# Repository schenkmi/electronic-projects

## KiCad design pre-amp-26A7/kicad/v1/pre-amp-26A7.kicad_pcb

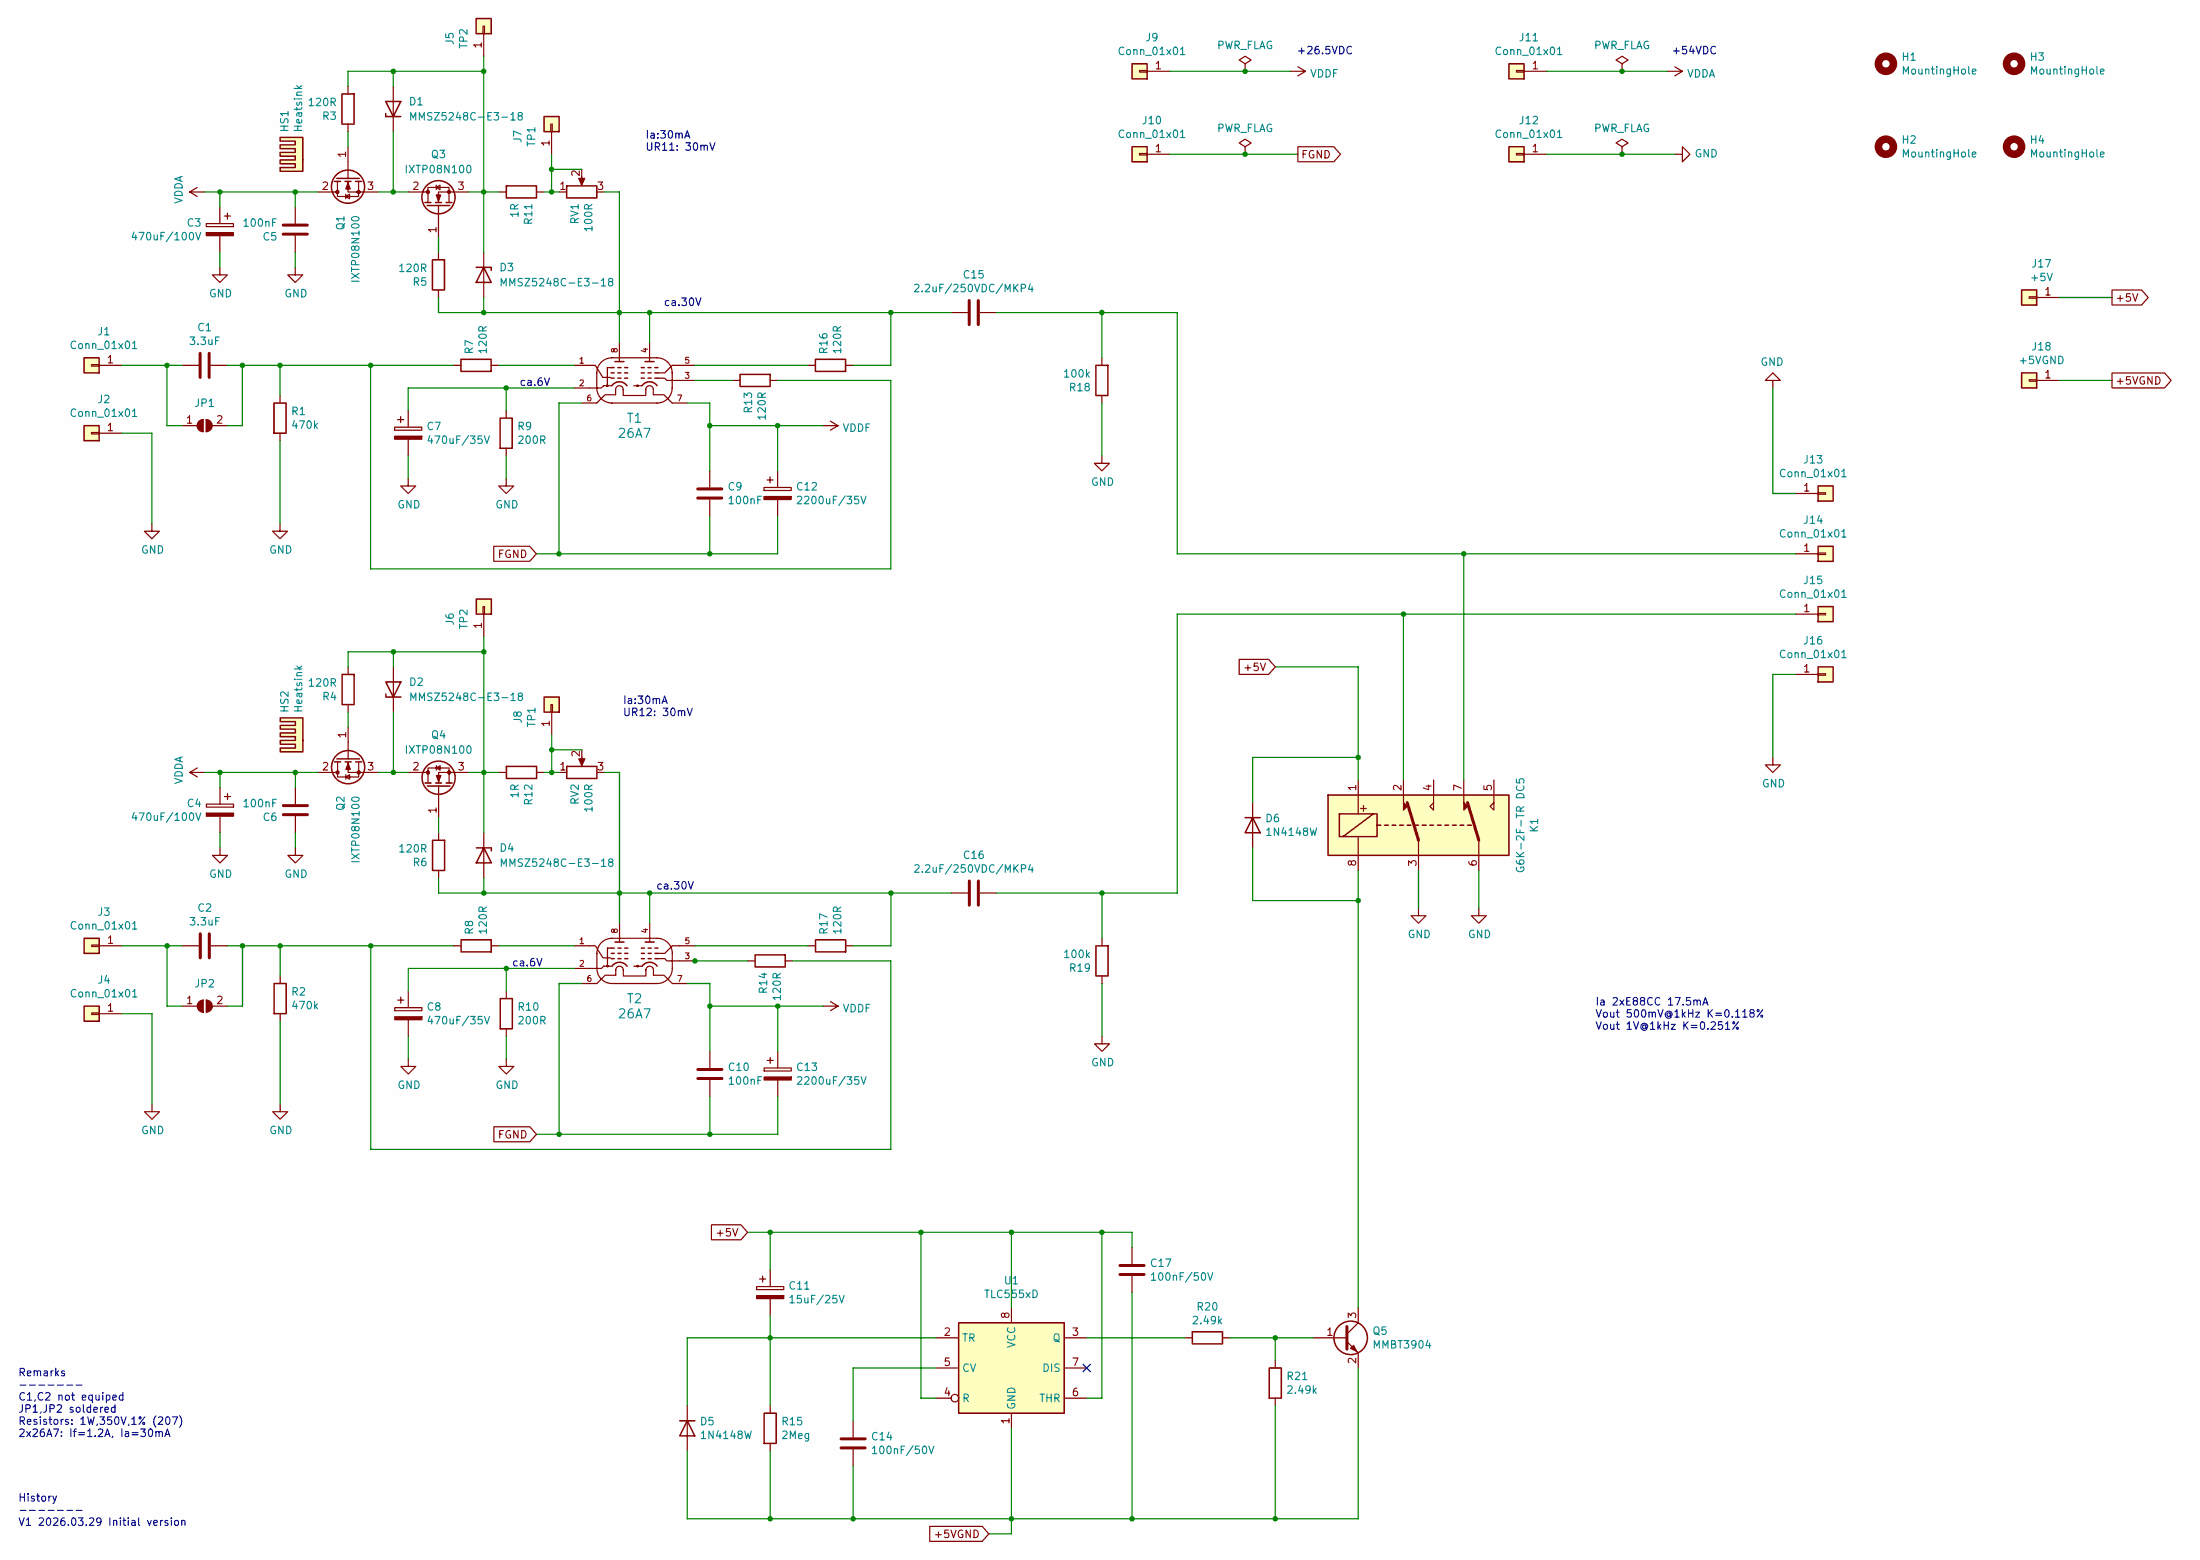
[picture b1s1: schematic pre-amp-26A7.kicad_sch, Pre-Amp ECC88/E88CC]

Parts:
C1, C2: 3.3uF; C_Rect_L7.2mm_W7.2mm_P5.00mm_FKS2_FKP2_MKS2_MKP2
C3, C4: 470uF/100V; CP_Radial_D18.0mm_P7.50mm
C5, C6, C9, C10: 100nF; C_Rect_L7.2mm_W2.5mm_P5.00mm_FKS2_FKP2_MKS2_MKP2
C7, C8: 470uF/35V; CP_Radial_D10.0mm_P5.00mm
C11: 15uF/25V; CP_EIA-3216-12_Kemet-S_HandSolder
C12, C13: 2200uF/35V; CP_Radial_D16.0mm_P7.50mm
C14, C17: 100nF/50V; C_0805_2012Metric_Pad1.18x1.45mm_HandSolder
C15, C16: 2.2uF/250VDC/MKP4; C_Rect_L31.5mm_W11.0mm_P27.50mm_MKS4
D1, D2, D3, D4: MMSZ5248C-E3-18; D_SOD-123
D5, D6: 1N4148W; D_SOD-123
H1, H2, H3, H4: MountingHole; MountingHole_3.2mm_M3_Pad_Via
HS1, HS2: Heatsink; Heatsink_Fischer_SK104-STC-STIC_35x13mm_2xDrill2.5mm
J1, J2, J3, J4, J13, J14, J15, J16: Conn_01x01; Pin_D1.0mm_L10.0mm
J5, J6: TP2; Pin_D1.0mm_L10.0mm
J7, J8: TP1; Pin_D1.0mm_L10.0mm
J9, J10, J11, J12: Conn_01x01; Pin_D1.3mm_L11.0mm
J17: +5V; Pin_D1.3mm_L11.0mm
J18: +5VGND; Pin_D1.3mm_L11.0mm
JP1, JP2: SolderJumper_2_Open; SolderJumper-2_P1.3mm_Open_Pad1.0x1.5mm
K1: G6K-2F-TR DC5; Relay_DPDT_Omron_G6K-2F
Q1, Q2, Q3, Q4: IXTP08N100; TO-220-3_Vertical
Q5: MMBT3904; SOT-23
R1, R2: 470k; R_MELF_MMB-0207
R3, R4, R5, R6, R7, R8, R13, R14, R16, R17: 120R; R_MELF_MMB-0207
R9, R10: 200R; R_MELF_MMB-0207
R11, R12: 1R; R_MELF_MMB-0207
R15: 2Meg; R_0805_2012Metric_Pad1.20x1.40mm_HandSolder
R18, R19: 100k; R_MELF_MMB-0207
R20, R21: 2.49k; R_0805_2012Metric_Pad1.20x1.40mm_HandSolder
RV1, RV2: 100R; Potentiometer_Bourns_3296W_Vertical
T1, T2: 26A7; TubeOctal
U1: TLC555xD; SOIC-8_3.9x4.9mm_P1.27mm

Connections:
+5V: C11.1, C17.1, D6.1 (K), J17.1 (Pin_1_1), K1.1, U1.4 (R), U1.6 (THR), U1.8 (VCC)
+5VGND: C14.2, C17.2, D5.2 (A), J18.1 (Pin_1_1), Q5.2 (E), R15.2, R21.2, U1.1 (GND)
FGND: C9.2, C10.2, C12.2, C13.2, J10.1 (Pin_1_1), T1.6 (h), T2.6 (h)
GND: C3.2, C4.2, C5.1, C6.1, C7.2, C8.2, J2.1 (Pin_1_1), J4.1 (Pin_1_1), J12.1 (Pin_1_1), J13.1 (Pin_1_1), J16.1 (Pin_1_1), K1.3, K1.6, R1.2, R2.2, R9.2, R10.2, R18.1, R19.1
unnamed: D1.2 (A), D3.1 (K), J5.1 (Pin_1_1), Q3.3 (S), R3.2, R11.2
unnamed: D1.1 (K), Q1.3 (S), Q3.2 (D)
unnamed: D2.2 (A), D4.1 (K), J6.1 (Pin_1_1), Q4.3 (S), R4.2, R12.2
unnamed: D2.1 (K), Q2.3 (S), Q4.2 (D)
unnamed: C15.2, D3.2 (A), R5.1, R16.2, RV1.3, T1.4 (p), T1.8 (p)
unnamed: C16.2, D4.2 (A), R6.1, R17.2, RV2.3, T2.4 (p), T2.8 (p)
unnamed: C11.2, D5.1 (K), R15.1, U1.2 (TR)
unnamed: D6.2 (A), K1.8, Q5.3 (C)
unnamed: C1.2, J1.1 (Pin_1_1), JP1.1 (A)
unnamed: C2.2, J3.1 (Pin_1_1), JP2.1 (A)
unnamed: J7.1 (Pin_1_1), R11.1, RV1.1, RV1.2
unnamed: J8.1 (Pin_1_1), R12.1, RV2.1, RV2.2
unnamed: C15.1, J14.1 (Pin_1_1), K1.7, R18.2
unnamed: C16.1, J15.1 (Pin_1_1), K1.2, R19.2
unnamed: C1.1, JP1.2 (B), R1.1, R7.1, R13.2
unnamed: C2.1, JP2.2 (B), R2.1, R8.1, R14.2
unnamed: Q1.1 (G), R3.1
unnamed: Q2.1 (G), R4.1
unnamed: Q3.1 (G), R5.2
unnamed: Q4.1 (G), R6.2
unnamed: Q5.1 (B), R20.1, R21.1
unnamed: R7.2, T1.1 (s)
unnamed: R8.2, T2.1 (s)
unnamed: R16.1, T1.5 (s)
unnamed: R17.1, T2.5 (s)
unnamed: R13.1, T1.3 (g)
unnamed: C7.1, R9.1, T1.2 (ks)
unnamed: R14.1, T2.3 (g)
unnamed: C8.1, R10.1, T2.2 (ks)
unnamed: C14.1, U1.5 (CV)
unnamed: R20.2, U1.3 (Q)
VDDA: C3.1, C4.1, C5.2, C6.2, J11.1 (Pin_1_1), Q1.2 (D), Q2.2 (D)
VDDF: C9.1, C10.1, C12.1, C13.1, J9.1 (Pin_1_1), T1.7 (h), T2.7 (h)

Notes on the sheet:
Remarks ------- C1,C2 not equiped JP1,JP2 soldered Resistors: 1W,350V,1% (207) 2x26A7: If=1.2A, Ia=30mA
ca.30V
Ia 2xE88CC 17.5mA Vout 500mV@1kHz K=0.118% Vout 1V@1kHz K=0.251%
Ia:30mA UR12: 30mV
History ------- V1 2026.03.29 Initial version
ca.6V
+26.5VDC
+54VDC
Ia:30mA UR11: 30mV

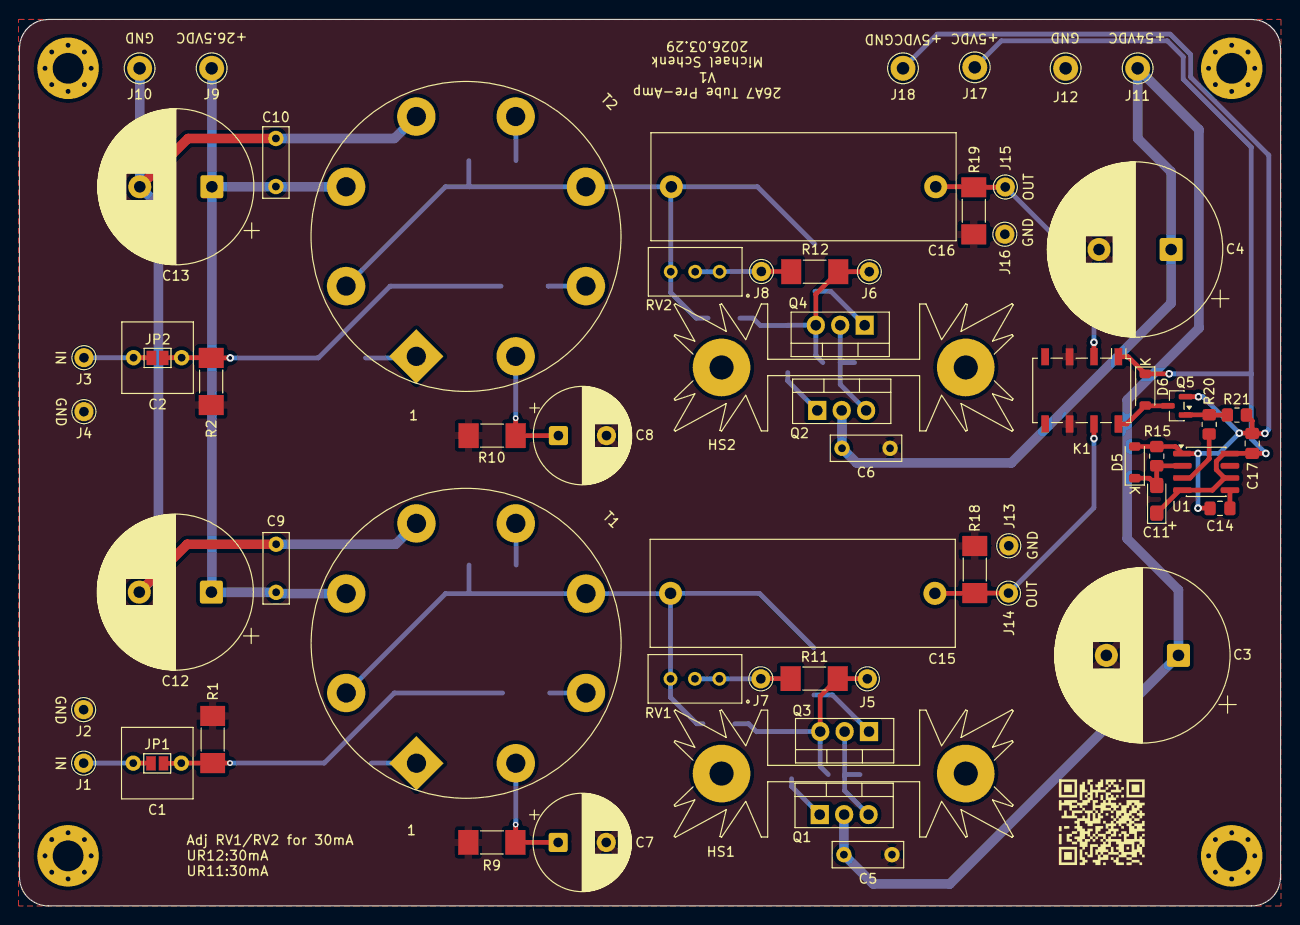
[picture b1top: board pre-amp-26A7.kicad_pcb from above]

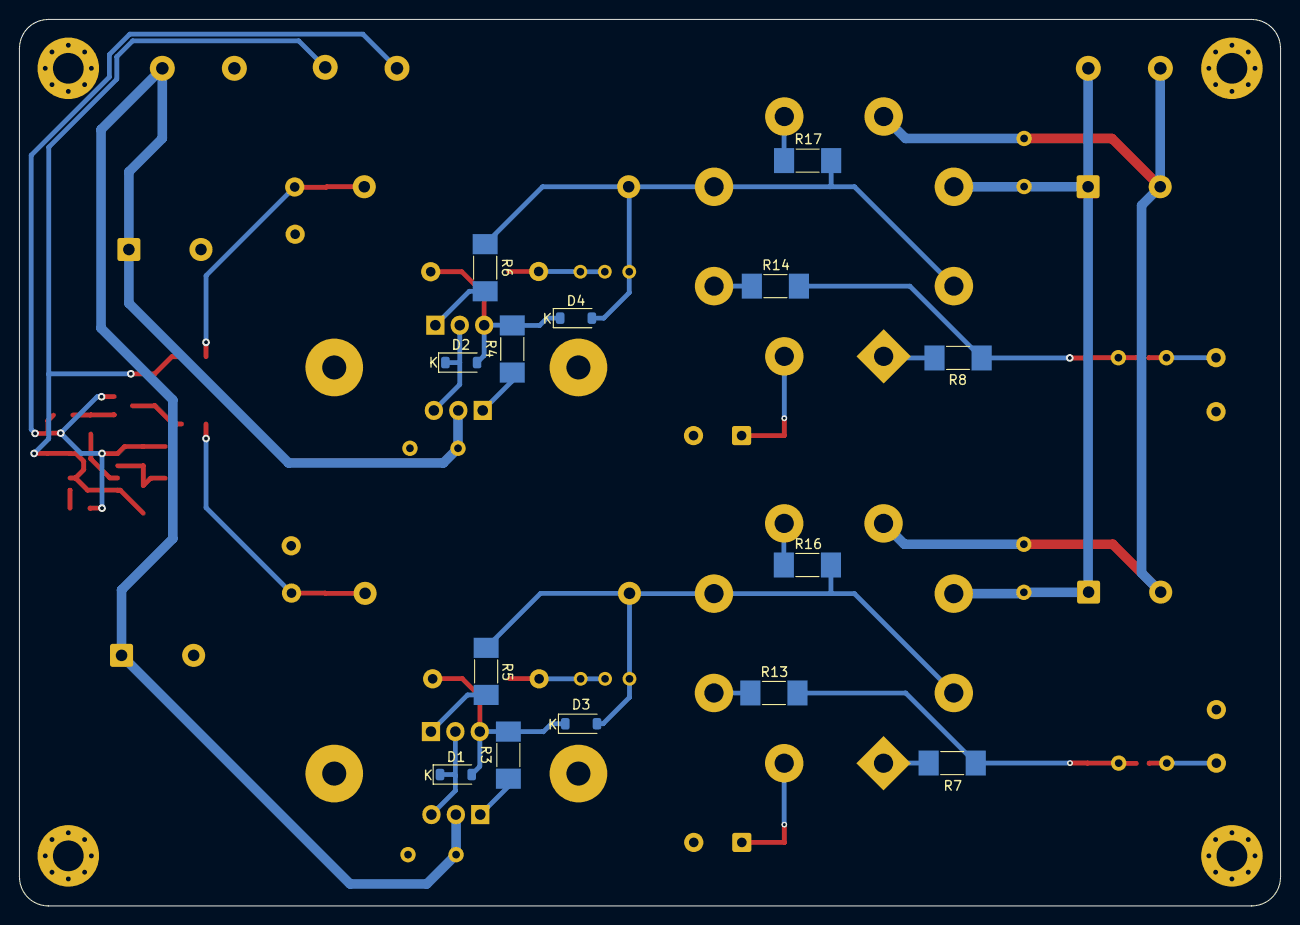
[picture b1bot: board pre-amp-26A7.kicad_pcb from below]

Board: 2 copper layers, 131.2 x 92.2 mm, 81 parts (14 on the bottom side), 37 nets.

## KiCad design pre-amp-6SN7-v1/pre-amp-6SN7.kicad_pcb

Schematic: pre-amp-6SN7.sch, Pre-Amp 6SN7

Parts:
C1, C5: 3.3uF; C_Rect_L7.2mm_W7.2mm_P5.00mm_FKS2_FKP2_MKS2_MKP2
C2, C8: 100nF; C_Rect_L18.0mm_W5.0mm_P15.00mm_FKS3_FKP3
C3, C9: 100uF; CP_Radial_D18.0mm_P7.50mm
C4, C10: 2.2uF; C_Rect_L31.5mm_W11.0mm_P27.50mm_MKS4
C6, C11: 100nF; C_Rect_L7.2mm_W2.5mm_P5.00mm_FKS2_FKP2_MKS2_MKP2
C7, C12: 2200uF; CP_Radial_D16.0mm_P7.50mm
D1, D2: 1N4007; D_SOD-123F
H1, H2, H3, H4: MountingHole; MountingHole_3.2mm_M3
J1, J3: IN; Pin_D1.0mm_L10.0mm
J2, J4: GNDIN; Pin_D1.0mm_L10.0mm
J5: HV; Pin_D1.3mm_L11.0mm
J6: GNDHV; Pin_D1.3mm_L11.0mm
J7, J11: OUT; Pin_D1.0mm_L10.0mm
J8, J12: GNDOUT; Pin_D1.0mm_L10.0mm
J9: LV1; Pin_D1.3mm_L11.0mm
J10, J14: GNDLV; Pin_D1.3mm_L11.0mm
J13: LV2; Pin_D1.3mm_L11.0mm
R1, R9, R10, R20: 1Meg; R_MELF_MMB-0207
R2, R11: 47k; R_MELF_MMB-0207
R3, R13: 1k; R_MELF_MMB-0207
R4, R5, R12, R15, R18, R19, R22, R24: 47k/1W; R_MELF_MMB-0207
R6, R17: 100k; R_MELF_MMB-0207
R7, R8, R14, R16: 100R; R_MELF_MMB-0207
T1, T2: 6SN7GT; TubeOctal

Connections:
GND: C2.2, C3.2, C6.2, C7.2, C8.2, C9.2, C11.2, C12.2, J2.1, J4.1, J6.1, J8.1, J10.1, J12.1, J14.1, R1.2, R3.2, R9.2, R10.2, R13.2, R18.2, R19.2, R20.2, R22.2, R24.2, T1.8 (h), T2.8 (h)
unnamed: C1.1, R1.1, R2.2
unnamed: C1.2, J3.1
unnamed: C4.1, J7.1, R6.1, R9.1
unnamed: C4.2, D1.1, R22.1, R24.1, T1.6 (kT2)
unnamed: C5.1, R10.1, R11.2
unnamed: C5.2, J1.1
unnamed: C10.1, J11.1, R17.1, R20.1
unnamed: C10.2, D2.1, R18.1, R19.1, T2.6 (kT2)
unnamed: D1.2, R4.2, R5.2, R8.2, T1.2 (qT1)
unnamed: D2.2, R12.2, R15.2, R16.2, T2.2 (qT1)
unnamed: R2.1, R6.2, R7.2
unnamed: R3.1, T1.3 (kT1)
unnamed: R7.1, T1.1 (gT1)
unnamed: R8.1, T1.4 (gT2)
unnamed: R11.1, R14.2, R17.2
unnamed: R13.1, T2.3 (kT1)
unnamed: R14.1, T2.1 (gT1)
unnamed: R16.1, T2.4 (gT2)
VDDA: C2.1, C3.1, C8.1, C9.1, J5.1, R4.1, R5.1, R12.1, R15.1, T1.5 (qT2), T2.5 (qT2)
VDDF1: C11.1, C12.1, J9.1, T1.7 (h)
VDDF2: C6.1, C7.1, J13.1, T2.7 (h)

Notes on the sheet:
LV: 6.3VDC / 1.2A HV: 300VDC / 26mA

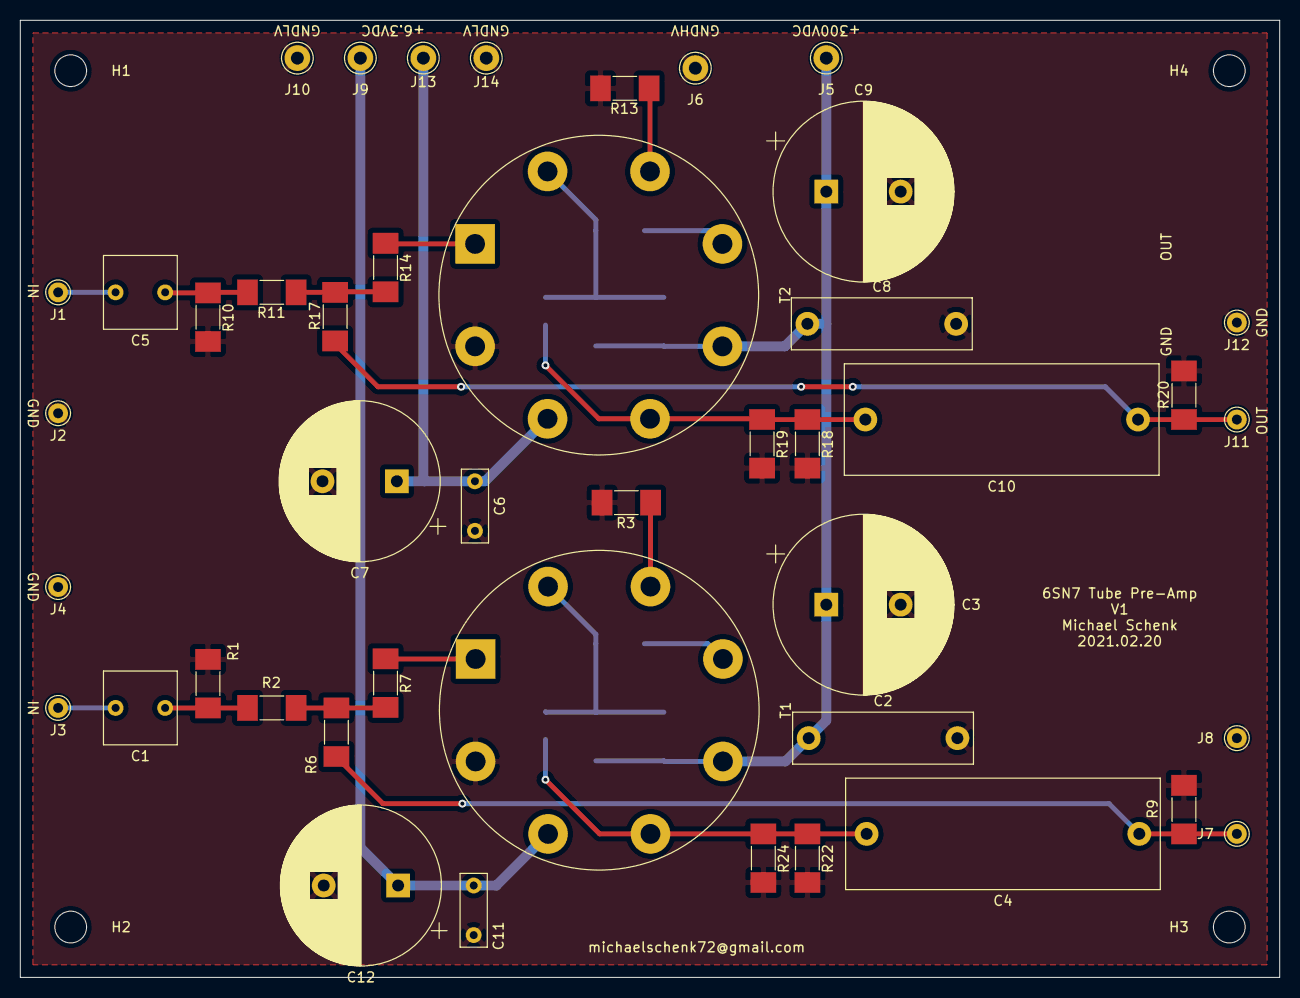
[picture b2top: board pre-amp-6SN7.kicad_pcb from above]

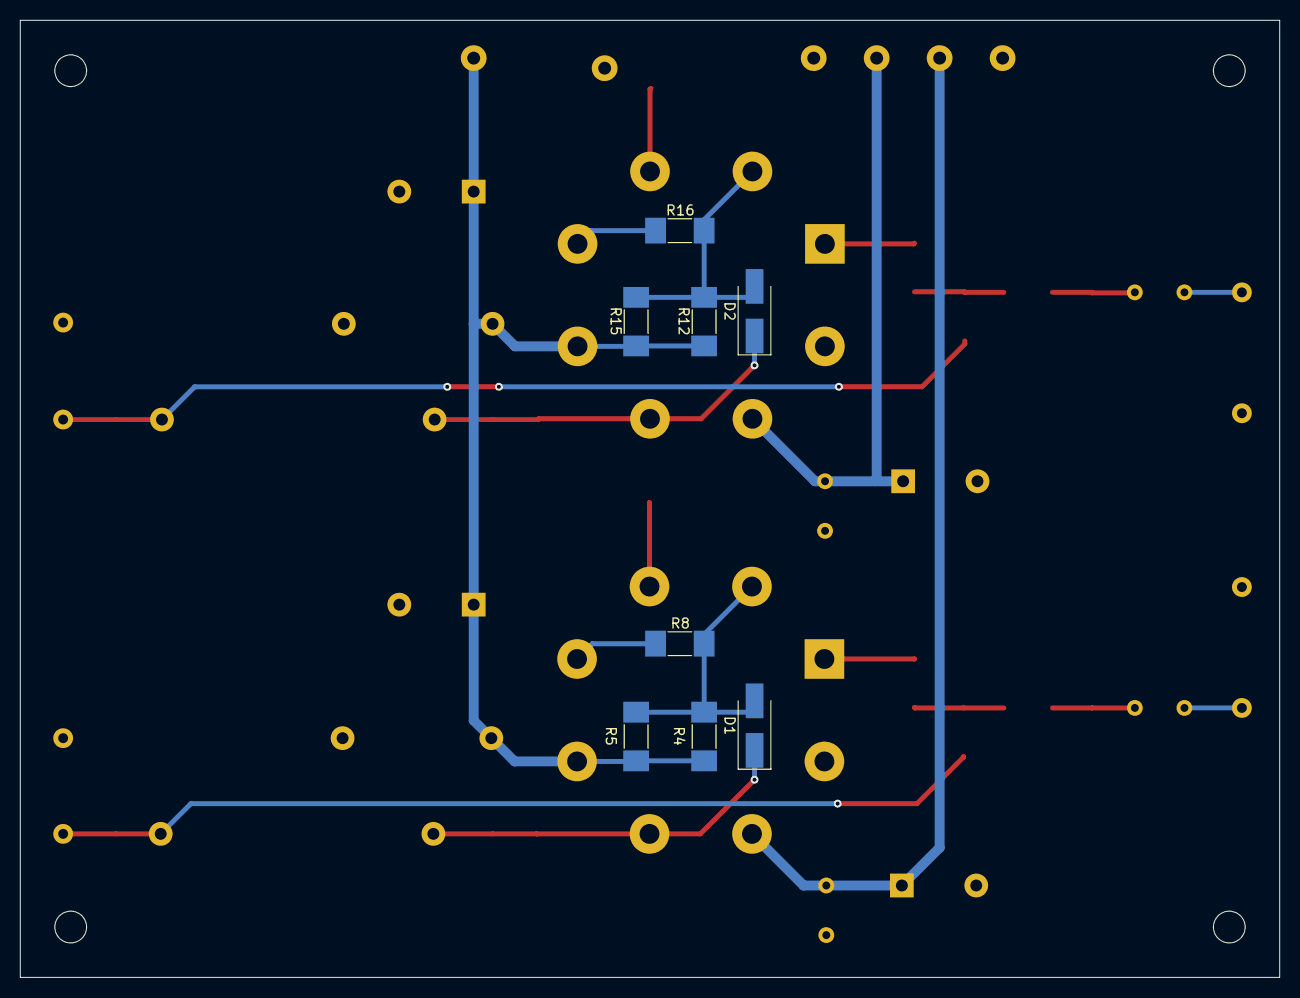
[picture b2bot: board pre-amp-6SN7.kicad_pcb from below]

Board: 2 copper layers, 127.0 x 96.5 mm, 56 parts (8 on the bottom side), 22 nets.

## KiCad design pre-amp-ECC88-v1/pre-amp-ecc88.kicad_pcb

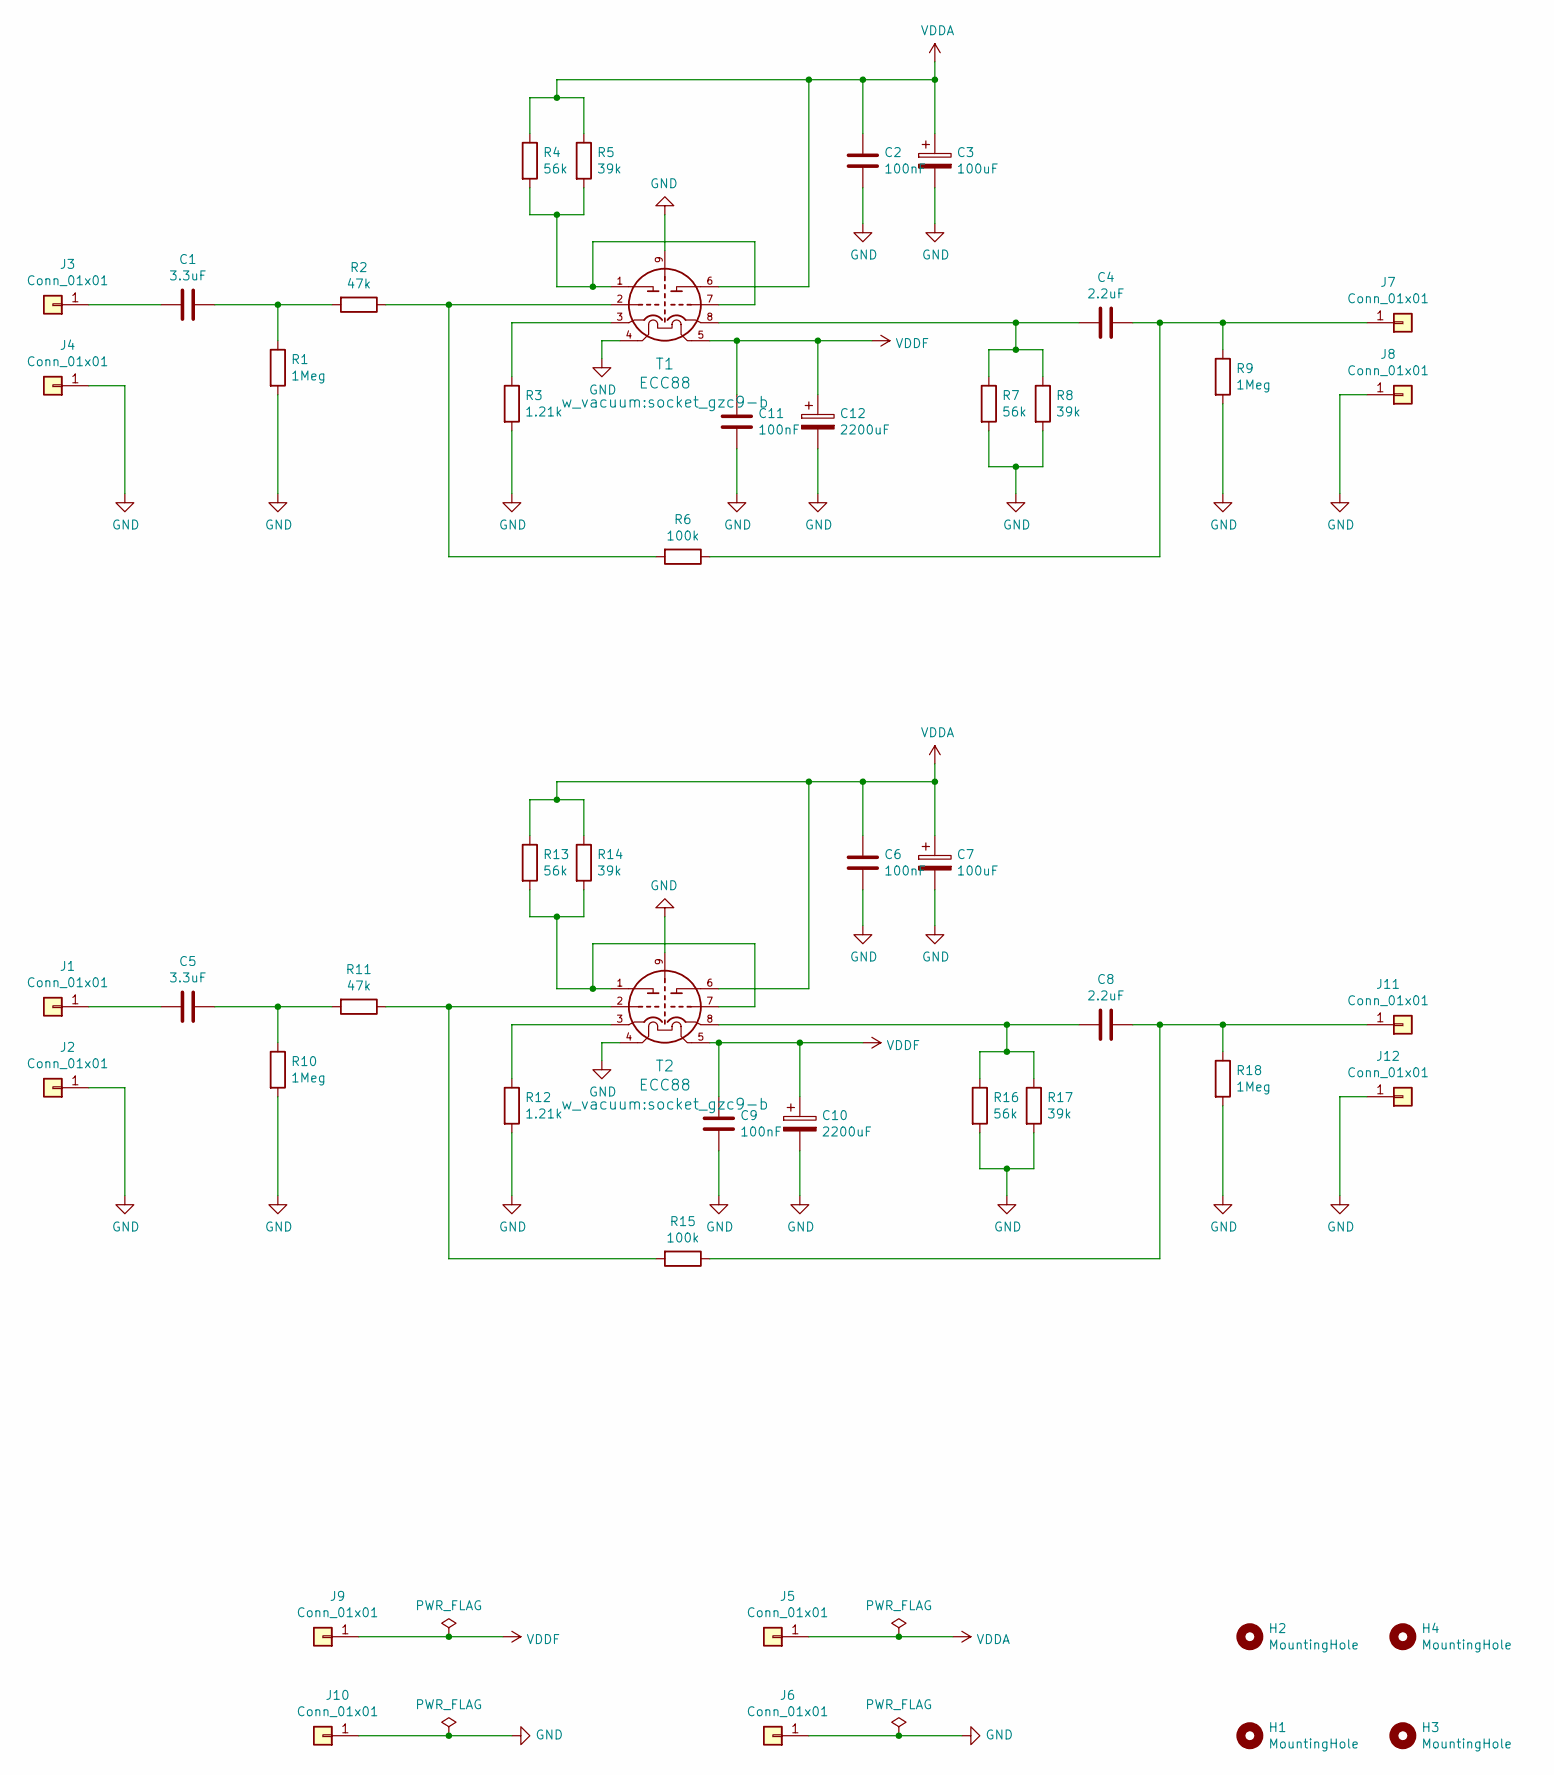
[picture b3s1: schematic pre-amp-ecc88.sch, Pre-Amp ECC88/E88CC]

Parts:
C1, C5: 3.3uF; C_Rect_L7.2mm_W7.2mm_P5.00mm_FKS2_FKP2_MKS2_MKP2
C2, C6: 100nF; C_Rect_L16.5mm_W5.0mm_P15.00mm_MKT
C3, C7: 100uF; CP_Radial_D18.0mm_P7.50mm
C4, C8: 2.2uF; C_Rect_L31.5mm_W9.0mm_P27.50mm_MKS4
C9, C11: 100nF; C_Rect_L7.2mm_W2.5mm_P5.00mm_FKS2_FKP2_MKS2_MKP2
C10, C12: 2200uF; CP_Radial_D16.0mm_P7.50mm
H1, H2, H3, H4: MountingHole; MountingHole_3.2mm_M3
J1, J2, J3, J4, J7, J8, J11, J12: Conn_01x01; Pin_D1.0mm_L10.0mm
J5, J6, J9, J10: Conn_01x01; Pin_D1.3mm_L11.0mm
R1, R9, R10, R18: 1Meg; R_MELF_MMB-0207
R2, R11: 47k; R_MELF_MMB-0207
R3, R12: 1.21k; R_MiniMELF_MMA-0204
R4, R7, R13, R16: 56k; R_MELF_MMB-0207
R5, R8, R14, R17: 39k; R_MELF_MMB-0207
R6, R15: 100k; R_MELF_MMB-0207
T1, T2: ECC88; socket_gzc9-b

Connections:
GND: C2.2, C3.2, C6.2, C7.2, C9.2, C10.2, C11.2, C12.2, J2.1, J4.1, J6.1, J8.1, J10.1, J12.1, R1.2, R3.2, R7.2, R8.2, R9.2, R10.2, R12.2, R16.2, R17.2, R18.2, T1.4 (h), T1.9 (s), T2.4 (h), T2.9 (s)
unnamed: C1.1, R1.1, R2.2
unnamed: C1.2, J3.1
unnamed: C4.1, J7.1, R6.1, R9.1
unnamed: C4.2, R7.1, R8.1, T1.8 (kT2)
unnamed: C5.1, R10.1, R11.2
unnamed: C5.2, J1.1
unnamed: C8.1, J11.1, R15.1, R18.1
unnamed: C8.2, R16.1, R17.1, T2.8 (kT2)
unnamed: R2.1, R6.2, T1.2 (gT1)
unnamed: R3.1, T1.3 (kT1)
unnamed: R4.2, R5.2, T1.1 (qT1), T1.7 (gT2)
unnamed: R11.1, R15.2, T2.2 (gT1)
unnamed: R12.1, T2.3 (kT1)
unnamed: R13.2, R14.2, T2.1 (qT1), T2.7 (gT2)
VDDA: C2.1, C3.1, C6.1, C7.1, J5.1, R4.1, R5.1, R13.1, R14.1, T1.6 (qT2), T2.6 (qT2)
VDDF: C9.1, C10.1, C11.1, C12.1, J9.1, T1.5 (h), T2.5 (h)

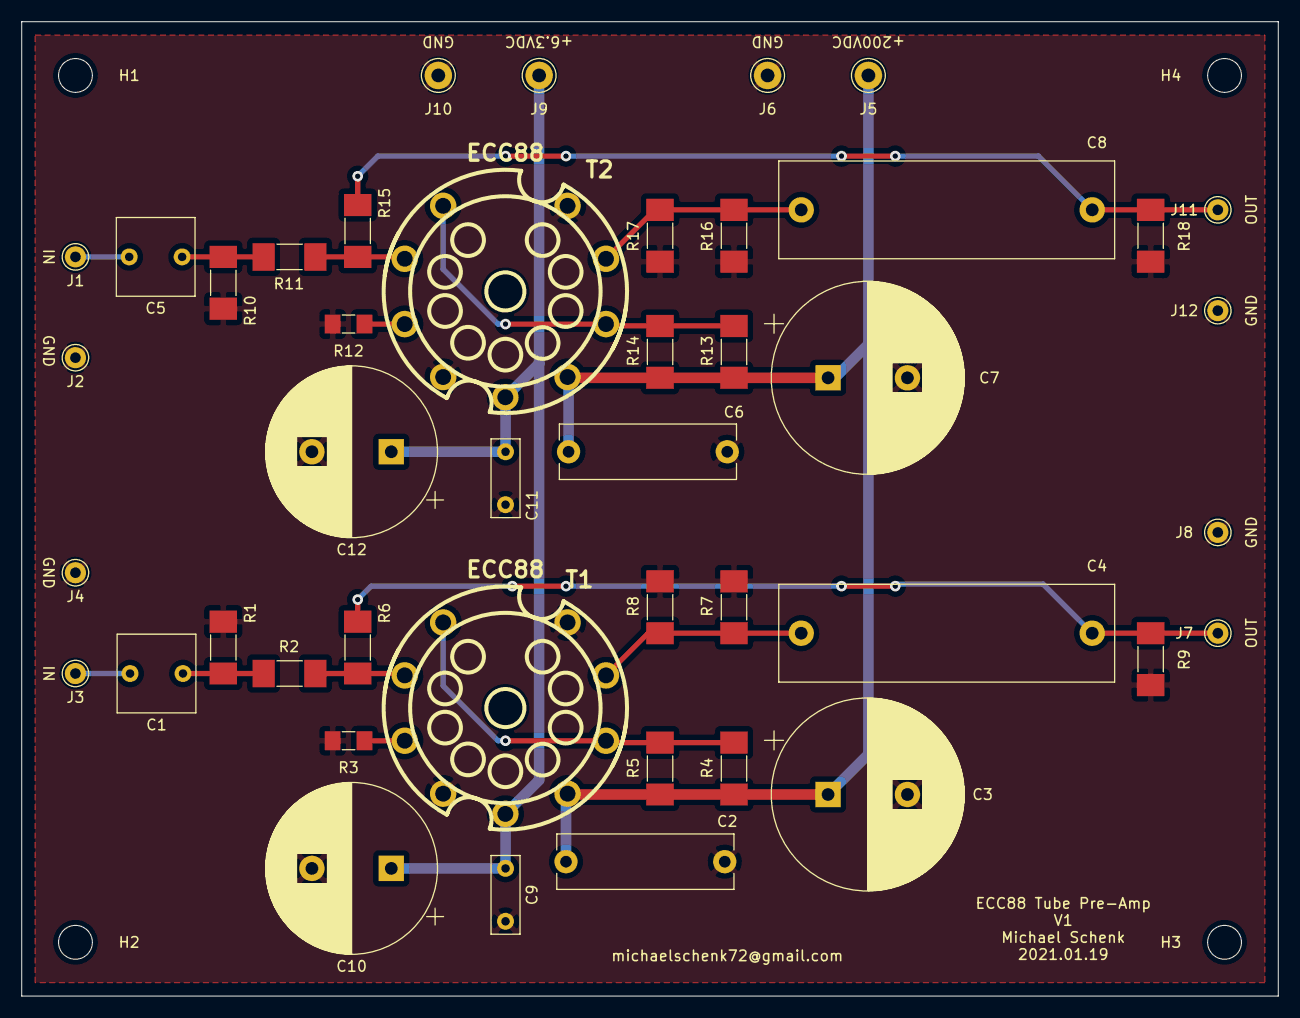
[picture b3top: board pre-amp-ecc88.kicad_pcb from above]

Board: 2 copper layers, 118.7 x 92.1 mm, 48 parts (0 on the bottom side), 17 nets.
